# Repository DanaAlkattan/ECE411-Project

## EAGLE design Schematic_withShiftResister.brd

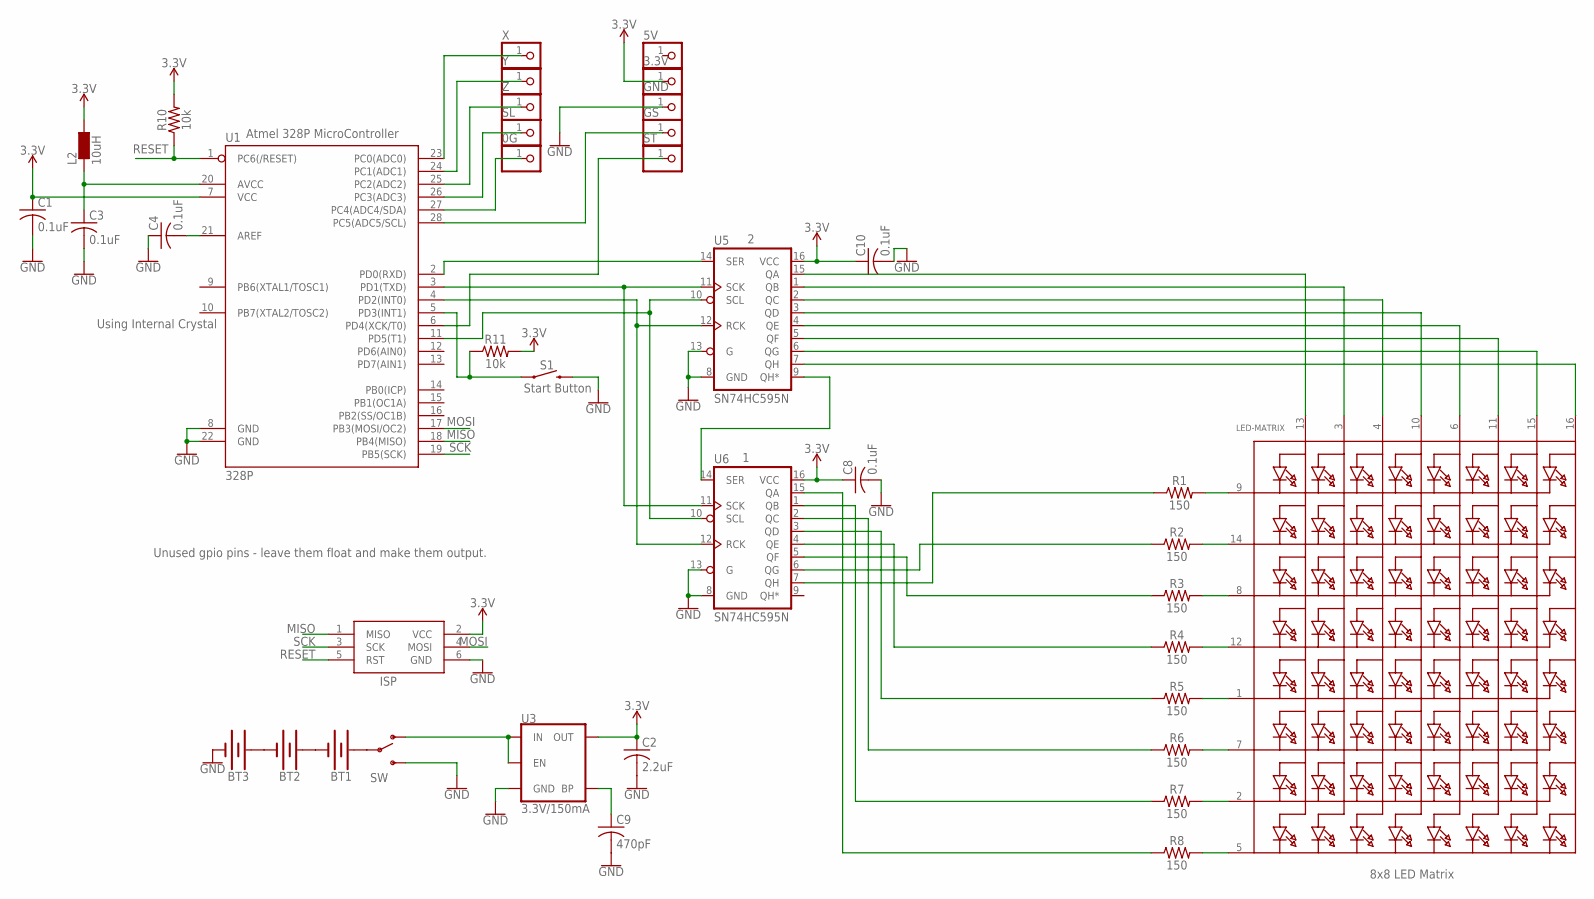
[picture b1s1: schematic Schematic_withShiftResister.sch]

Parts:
0G, 3.3V, 5V: PINHD-1X1; 1X01
BT1, BT2, BT3: BATTERY-AAA_KIT; BATTERY-AAA-KIT
C1, C3, C4, C8, C10: 0.1uF; C0805
C2: 2.2uF; C0805
C9: 470pF; C0805
GND: PINHD-1X1; 1X01
GS: PINHD-1X1; 1X01
ISP: AVRISP-6; AVRISP
L2: 10uH; L1812
LED-MATRIX: SEGMENT_8X8_ROWCATHODEM12A881UR; SEGMENT_BL-M12A881UR
R1, R2, R3, R4, R5, R6, R7, R8: 150; 0603
R10, R11: 10k; 0603
S1: MOMENTARY-SWITCH-SPST-PTH-6.0MM; TACTILE_SWITCH_PTH_6.0MM
SL: PINHD-1X1; 1X01
ST: PINHD-1X1; 1X01
SW: SWITCH-SPSTPTH_LOCK; SWITCH-SPDT_LOCK.007S
U1: 328P; DIP28
U3: 3.3V/150mA; SOT23-5
U5, U6: SN74HC595N; DIP16
X: PINHD-1X1; 1X01
Y: PINHD-1X1; 1X01
Z: PINHD-1X1; 1X01

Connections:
3.3V: 3.3V.1, C1.1, C2.1, C8.1, C10.1, ISP.2 (VCC), L2.1, R10.2, R11.2, U1.7 (VCC), U3.5 (OUT), U5.16 (VCC), U6.16 (VCC)
GND: BT3.GND@1 (-), C1.2, C2.2, C3.2, C4.1, C8.2, C9.2, C10.2, GND.1, ISP.6 (GND), S1.3 (2), SW.3 (S), U1.8 (GND), U1.22 (GND), U3.2 (GND), U5.8 (GND), U5.13 (G), U6.8 (GND), U6.13 (G)
MISO: ISP.1 (MISO), U1.18 (PB4(MISO))
MOSI: ISP.4 (MOSI), U1.17 (PB3(MOSI/OC2))
unnamed: LED-MATRIX.9 (K1), R1.2
unnamed: LED-MATRIX.14 (K2), R2.2
unnamed: LED-MATRIX.8 (K3), R3.2
unnamed: LED-MATRIX.1 (K5), R5.2
unnamed: LED-MATRIX.7 (K6), R6.2
unnamed: LED-MATRIX.2 (K7), R7.2
unnamed: LED-MATRIX.5 (K8), R8.2
unnamed: LED-MATRIX.13 (A1), U5.15 (QA)
unnamed: LED-MATRIX.4 (A3), U5.2 (QC)
unnamed: LED-MATRIX.10 (A4), U5.3 (QD)
unnamed: LED-MATRIX.6 (A5), U5.4 (QE)
unnamed: LED-MATRIX.11 (A6), U5.5 (QF)
unnamed: LED-MATRIX.15 (A7), U5.6 (QG)
unnamed: LED-MATRIX.16 (A8), U5.7 (QH)
unnamed: R8.1, U6.15 (QA)
unnamed: U1.23 (PC0(ADC0)), X.1
unnamed: U1.24 (PC1(ADC1)), Y.1
unnamed: U1.25 (PC2(ADC2)), Z.1
unnamed: R7.1, U6.1 (QB)
unnamed: R6.1, U6.2 (QC)
unnamed: R5.1, U6.3 (QD)
unnamed: R4.1, U6.4 (QE)
unnamed: R3.1, U6.5 (QF)
unnamed: R2.1, U6.6 (QG)
unnamed: R1.1, U6.7 (QH)
unnamed: LED-MATRIX.3 (A2), U5.1 (QB)
unnamed: U1.3 (PD1(TXD)), U5.11 (SCK), U6.11 (SCK)
unnamed: SW.1 (O), U3.1 (IN), U3.3 (EN)
unnamed: BT2.GND@1 (-), BT3.PWR@1 (+)
unnamed: BT1.GND@1 (-), BT2.PWR@1 (+)
unnamed: C9.1, U3.4 (BP)
unnamed: U1.2 (PD0(RXD)), U5.14 (SER)
unnamed: U5.9 (QH*), U6.14 (SER)
unnamed: U1.4 (PD2(INT0)), U5.12 (RCK), U6.12 (RCK)
unnamed: BT1.PWR@1 (+), SW.2
unnamed: C4.2, U1.21 (AREF)
unnamed: U1.11 (PD5(T1)), U5.10 (SCL), U6.10 (SCL)
unnamed: R11.1, S1.1, U1.5 (PD3(INT1))
unnamed: SL.1, U1.26 (PC3(ADC3))
unnamed: 0G.1, U1.27 (PC4(ADC4/SDA))
unnamed: C3.1, L2.2, U1.20 (AVCC)
unnamed: GS.1, U1.28 (PC5(ADC5/SCL))
unnamed: ST.1, U1.6 (PD4(XCK/T0))
RESET: ISP.5 (RST), R10.1, U1.1 (PC6(/RESET))
SCK: ISP.3 (SCK), U1.19 (PB5(SCK))

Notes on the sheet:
Atmel 328P MicroController
8x8 LED Matrix
Start Button
Using Internal Crystal
Unused gpio pins - leave them float and make them output.

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
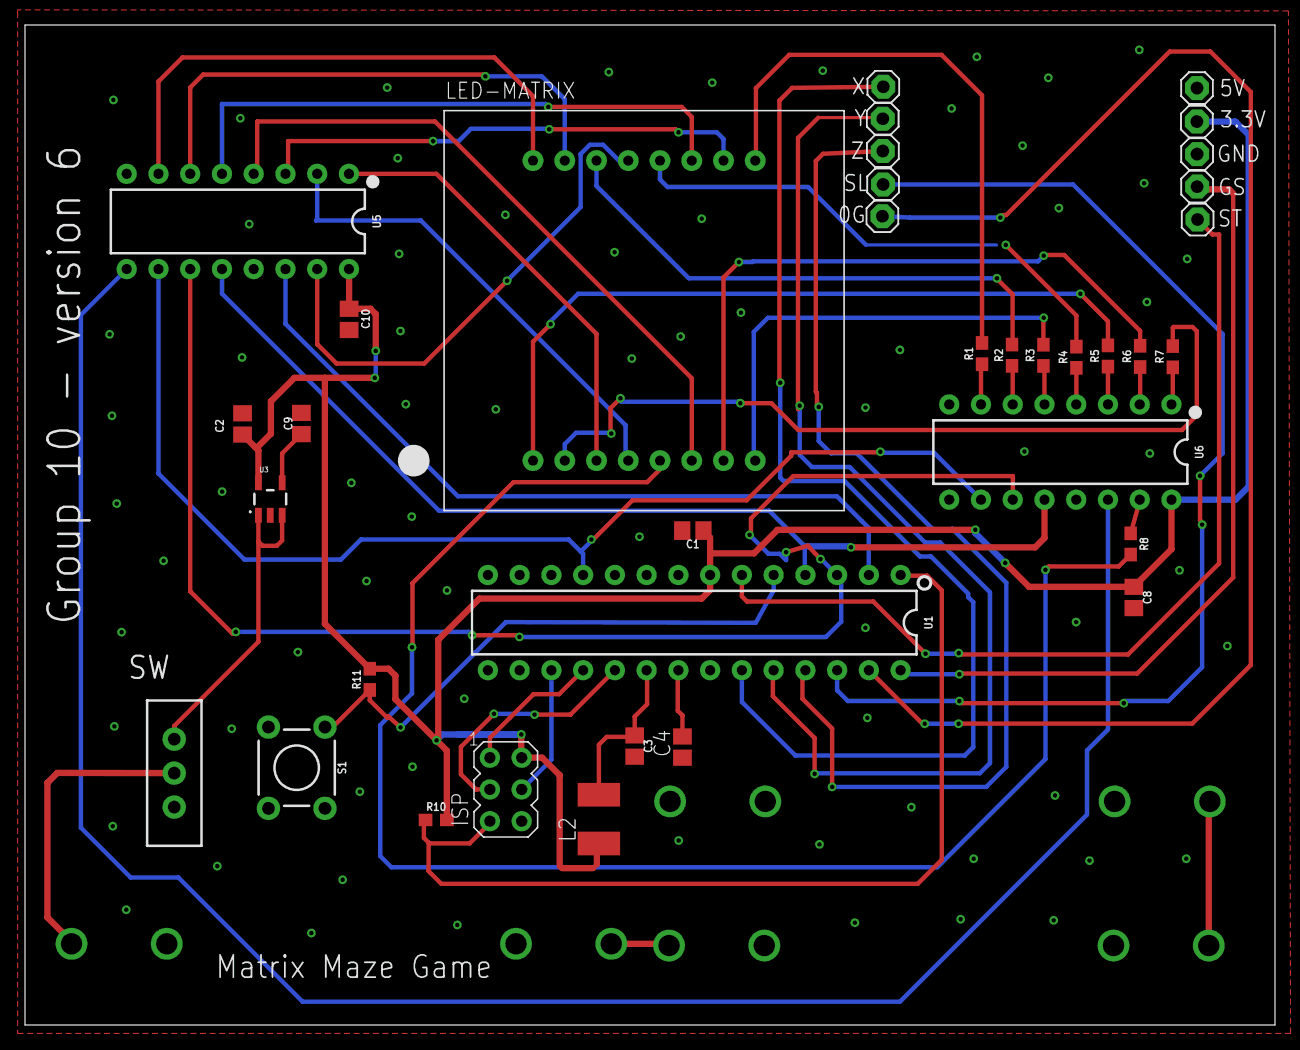
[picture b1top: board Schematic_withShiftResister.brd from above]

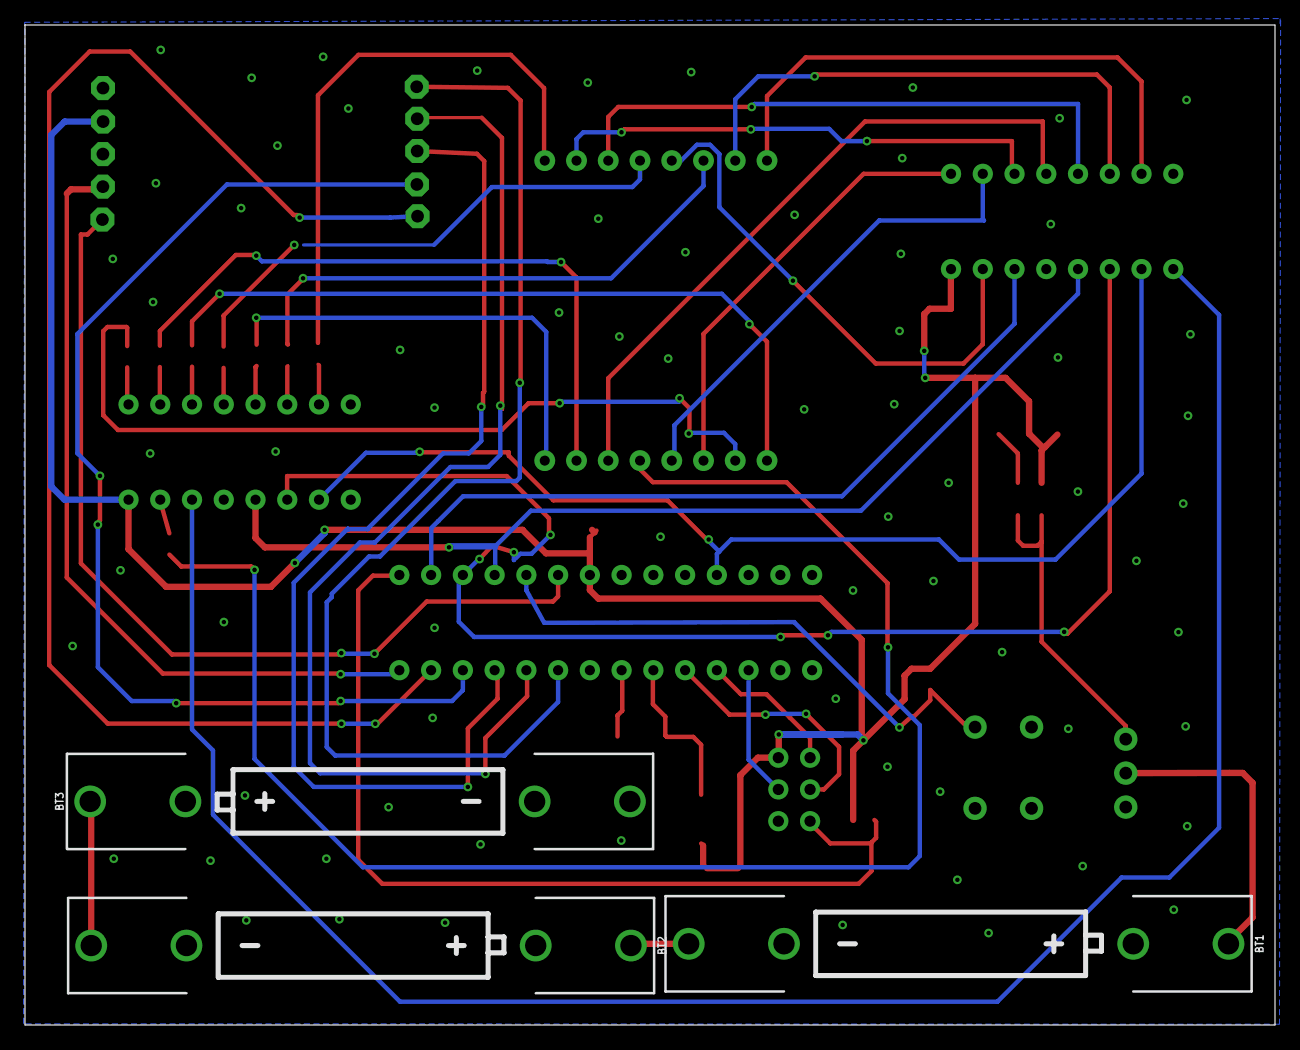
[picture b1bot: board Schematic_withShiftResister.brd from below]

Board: 2 copper layers, 100.0 x 80.0 mm, 39 parts (3 on the bottom side), 49 nets.

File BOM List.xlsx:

Qty | Value | Device | Package | Parts | Description | Unit Price | Extended Price | Price per Board | Datasheet
3 |  | BATTERY-AAA_KIT | BATTERY-AAA-KIT | BT1, BT2, BT3 | Battery - Single Cell | 0.4 | 10.80/27 | 2.4000000000000004 | http://www.mouser.com/ds/2/215/2-743115.pdf
10 |  | PINHD-1X1 | 1X01 | 0G, 3.3V, 5V, GND, GS, SL, ST, X, Y, Z | Pin header 1x1 for 0.1" spacing | 10.99 |  | 10.99 | https://dl.dropboxusercontent.com/content_link/imm0ZKoNwz7Tb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
1 |  | SEGMENT_8X8_ROWCATHODEM12A881UR | SEGMENT_BL-M12A881UR | LED-MATRIX | 8x8 LED Segment Displays: Row = Cathode | 6.93 |  | 6.93 | https://www.sparkfun.com/datasheets/Components/SanYoung-Medi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
1 |  | SWITCH-SPSTPTH_LOCK | SWITCH-SPDT_LOCK.007S | SW | SPST Switch | 0.106 | 5.31/ 50 | 0.106 | https://cdn.sparkfun.com/datasheets/Components/Switches/1193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
5 | 0.1 uF | C-USC0805 | C0805 | C1, C3, C4, C8, C10 | CAPACITOR, American symbol | 8.8999999999999996E-2 | 2.67/30 | 0.44499999999999995 | http://www.mouser.com/ds/2/212/KEM_C1023_X7R_AUTO_SMD-1093309.pdf
2 | 10 K | 10KOHM-0603-1/10W-1% | 603 | R10, R11 | 10kO resistor | 3.3000000000000002E-2 | 6.52/200 | 6.6000000000000003E-2 | http://www.mouser.com/ds/2/414/WIN-534129-1210153.pdf
1 | 10uH | L | L1812 | L2 | INDUCTOR, European symbol | 0.996 | 9.96/10 | 0.996 | http://www.mouser.com/ds/2/400/b82432a-1092831.pdf
8 | 150 | 150OHM-0603-1/10W-1% | 603 | R1, R2, R3, R4, R5, R6, R7, R8 | 150O resistor | 1.4999999999999999E-2 | 7.00/500 | 0.12 | http://www.mouser.com/ds/2/427/crcw0201e3-239671.pdf
1 | 2.2uF | C-USC0805 | C0805 | C2 | CAPACITOR, American symbol | 0.14899999999999999 | 1.49/10 | 0.14899999999999999 | http://www.mouser.com/ds/2/396/mlcc11_hq_e-541564.pdf
1 | 3.3V/150mA | V_REG_MIC52053.3V | SOT23-5 | U3 | V_REG MIC5205 Standard 3.3V, 5V | 0.48 | 2.40/5 | 0.48 | http://www.mouser.com/ds/2/268/mic5205-778789.pdf
1 | 328P | ATMEGA328P_PDIP | DIP28 | U1 | Atmel 328P | 4 |  | 4 | http://www.atmel.com/Images/Atmel-42735-8-bit-AVR-Microcontr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
1 | 470pF | C-USC0805 | C0805 | C9 | CAPACITOR, American symbol | 0.64 | 6.40/10 | 0.64 | http://www.mouser.com/ds/2/40/AVX-MM-1021715.pdf
1 | AVRISP-6 | AVRISP-6 | AVRISP | ISP | AVR ISP HEADER | 0.45 | 2.25/5 | 0.45 | N/A
1 | MOMENTARY-SWITCH-SPST-PTH-6.0MM | MOMENTARY-SWITCH-SPST-PTH-6.0MM | TACTILE_SWITCH_PTH_6.0MM | S1 | Momentary Switch (Pushbutton) - SPST | 0.06 | 5.99/100 | 0.06 | https://www.onlinecomponents.com/datasheet/mjtp1230.aspx?p=10578901
2 | SN74HC595N | 74HC595N | DIP16 | U5, U6 | 8-Bit Shift Register (Serial to Parallel) | 1.5 | 6.01/4 | 3 | https://www.sparkfun.com/datasheets/IC/SN74HC595.pdf
 |  |  |  |  | Cost per one Board = |  |  | 30.832000000000001

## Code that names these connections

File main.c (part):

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#define VOLTAGE 3.3

//ADC channels for accelerometer input
#define X_CHANNEL 0x40  // pin 23 - pc0
#define Y_CHANNEL 0x41	// pin 24 - pc1
#define Z_CHANNEL 0x42	// pin 25 - pc2

int currRow = 0;
int currCol = 0;
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*************************************************************************/
#define		HC595_DDR		DDRD		
#define		HC595_PORT		PORTD
#define		HC595_IN		PD0		//Data input to the first register
#define		HC595_CLOCK		PD1		//Clock signal
#define		HC595_LATCH		PD2		//Latch signal
#define		HC595_CLEAR		PD5		//Clear signal

/*************************************************************************
						HC595 Initialization
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*************************************************************************/
void Button_Init(void)
{
	DDRD &= ~(1 << PORTD3);		//Set PD3 for input
	//PORTD |= (1 << PORTD3);		// set PD2/INT0 (pin 4) internal pull-up resistor*/

	PCICR |= (1 << PCIE2);      //Set pin-change interrupt for D pins
	PCMSK2 |= (1 << PCINT19);   //Mask PCINT19
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	
	int randNumber = 0;	
	randNumber = rand() % 11; 								
	if (BIT_IS_CLEAR(PIND, PD3))
	{	
		Greet_Matrix(THREE);
		Greet_Matrix(TWO);
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
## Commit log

2017-10-26 Update PracticumSchematic
    Added pullup resistors to I2c. Added bypass capacitors to power supplies. Connected unused pins to Vcc. Connected SA0 pin on MMA8452 to ground. Added resistor to Vcc on Iset on MAX7219. Rotated batte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
2017-10-30 preliminary project file. some duties not set and lists not made
2017-11-02 Add files via upload
    Final project schedule with load leveling and milestones
2017-11-02 corrected errors
    separated buttons and leds. connect resistors between LEDs and GND. connect unused Atmega pins to GND. connect DIN on MAX 7219 to MOSI on atmega328. removed resistors btw outputs on MAX 7219. added R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
2017-11-25 arduino code ported to C

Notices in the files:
parts and their libraries:
SparkFun-Batteries: Licensing: Creative Commons ShareAlike 4.0 International - https://creativecommons.org/licenses/by-sa/4.0
